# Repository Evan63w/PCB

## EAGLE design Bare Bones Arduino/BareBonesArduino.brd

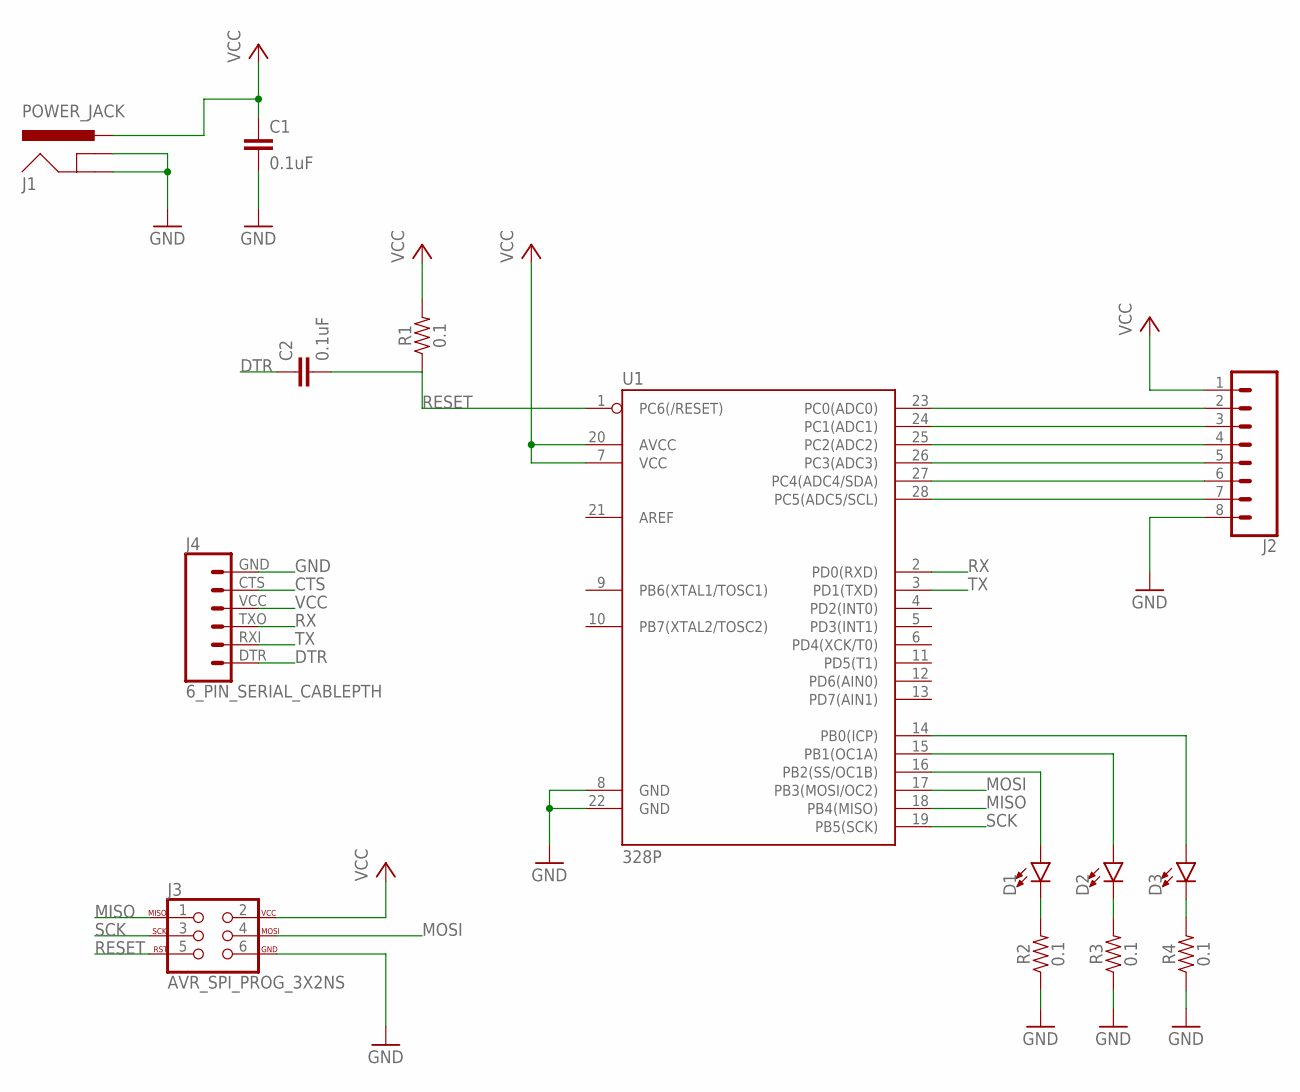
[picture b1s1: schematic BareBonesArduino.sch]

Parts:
C1, C2: 0.1uF; 0402
D1, D2, D3: LED5MM; LED_5MM
J1: POWER_JACK; POWER_JACK_PTH
J2: CONN_08"; 1X08
J3: AVR_SPI_PROG_3X2NS; 2X3-NS
J4: 6_PIN_SERIAL_CABLEPTH; FTDI_BASIC
R1, R2, R3, R4: 0.1; 1210
U1: 328P; DIP28

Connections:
CTS: J4.CTS (5)
DTR: C2.1, J4.DTR (1)
GND: C1.2, J1.GND, J1.GNDBREAK, J2.8, J3.6, J4.GND (6), R2.1, R3.1, R4.1, U1.8 (GND), U1.22 (GND)
MISO: J3.1, U1.18 (PB4(MISO))
MOSI: J3.4, U1.17 (PB3(MOSI/OC2))
unnamed: D1.A, U1.16 (PB2(SS/OC1B))
unnamed: D2.A, U1.15 (PB1(OC1A))
unnamed: D3.A, U1.14 (PB0(ICP))
unnamed: D3.K (C), R4.2
unnamed: D1.K (C), R2.2
unnamed: D2.K (C), R3.2
unnamed: J2.7, U1.28 (PC5(ADC5/SCL))
unnamed: J2.6, U1.27 (PC4(ADC4/SDA))
unnamed: J2.5, U1.26 (PC3(ADC3))
unnamed: J2.4, U1.25 (PC2(ADC2))
unnamed: J2.3, U1.24 (PC1(ADC1))
unnamed: J2.2, U1.23 (PC0(ADC0))
RESET: C2.2, J3.5, R1.1, U1.1 (PC6(/RESET))
RX: J4.TXO (3), U1.2 (PD0(RXD))
SCK: J3.3, U1.19 (PB5(SCK))
TX: J4.RXI (2), U1.3 (PD1(TXD))
VCC: C1.1, J1.PWR, J2.1, J3.2, J4.VCC (4), R1.2, U1.7 (VCC), U1.20 (AVCC)

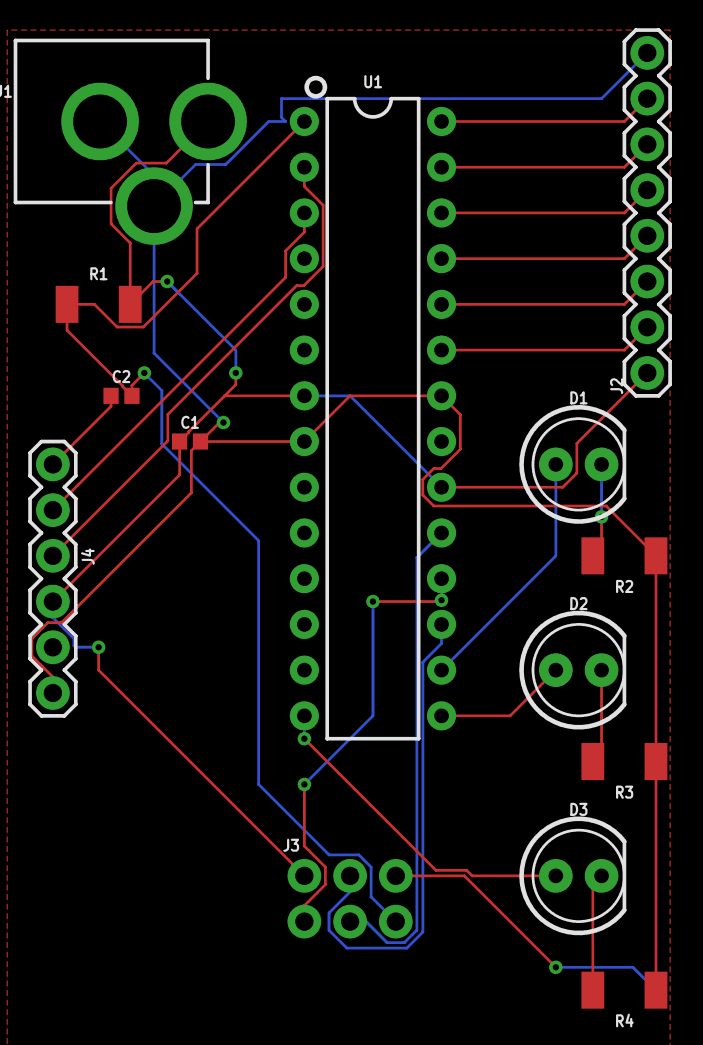
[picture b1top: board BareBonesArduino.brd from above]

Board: 2 copper layers, 14 parts (0 on the bottom side), 21 nets.

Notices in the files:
parts and their libraries:
SparkFun-Capacitors: Licensing: Creative Commons ShareAlike 4.0 International - https://creativecommons.org/licenses/by-sa/4.0
